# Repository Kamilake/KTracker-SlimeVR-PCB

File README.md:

# Move to the [FineMotion!](https://github.com/Kamilake/FineMotion-Tracker)
This repo is old and I created a new tracker. For non-maintenance purposes, go to:   
https://github.com/Kamilake/FineMotion-Tracker

# KTracker-SlimeVR-PCB
ESP8266 Attitude Tracker for SlimeVR

Full SMT PCB operating in MPU-6050 + QMC5883L 9DoF mode (or any breakout board compatible with GY-521)

Operate with all 5V chargers, including C to C PD chargers.

You can use it simply by ordering it from the fabricator

M.2 SSD size ultra-small form factor, Smallest size that can fit 18650!

## Available Battery

You can use any battery if you don't use the included modeling. or
1. 052050,052070,102050,102070 Size Li-Po (1000mAh) with JST PH 2.0mm Connector
2. 18650 battery (up to 4200mAh) with THT PIN 18650 Battery holder
3. 3x 1.5v battery (cannot be charged)

## Available Equipment 

## License
**This hardware is licensed under the CERN-OHL-P v2 license**, which is a permissive,
non-viral and non-reciprocal open hardware license. Unlike software licenses like
MIT and Apache 2.0, it better handles the nuances of hardware and protects both
the licensor and licensee from patent lawsuits.

**Unless you explicitly state otherwise, any contribution intentionally submitted
for inclusion in this work by you, shall be licensed as above, without any
additional terms or conditions.**

### Conveying notice of License
Note that as part of the CERN-OHL-P v2 license, recipients of manufactured
hardware must also receive notice of the above license. One such
method of conveying the notice is to include a link to the original source repo,
or printing "Licensed under CERN-OHL-P v2" on the PCB silkscreen. For more info,
see [here](https://ohwr.org/project/cernohl/wikis/Documents/CERN-OHL-version-2).

This is conceptually similar to the MIT/Apache 2.0 Licenses, where the original
license must still be included as a notice even when the source is modified and
subsequently relicensed under different terms.

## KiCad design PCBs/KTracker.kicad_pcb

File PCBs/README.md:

# Custom assembly using Kikit JLC

Due to JLCPCB's new assembly policy, soldering on the bottom side or using a non-black PCB will incur additional charges.   
Bottom side soldering is not possible if the "Economic" assembly option is selected.   

As the bottom side soldering is only for the connector, manual assembly is recommended.   

## Panalize and Fab
```batch
kikit panelize ^
    -p :jlcTooling ^
    --layout "grid; rows: 5; cols: 10;" ^
    --source "tolerance: 1000mm" ^
    --tabs full ^
    --cuts vcuts ./KamiTrack.kicad_pcb ^
    KamiTrack_panel.kicad_pcb

kikit fab jlcpcb ^
    --assembly ^
    --schematic ./KamiTrack.kicad_sch ^
    --ignore J1 ^
    --no-drc ./KamiTrack_panel.kicad_pcb ^
    ./fab
```

## Only Fab

### Using internal MPU-6050+QMC5883L and bottom Lipo
```batch
kikit fab jlcpcb ^
    --assembly ^
    --schematic ./KamiTrack.kicad_sch ^
    --ignore BT1,J3,J4,J5 ^
    --no-drc ./KamiTrack.kicad_pcb ^
    "./Gerber/Using internal MPU-6050+QMC5883L and bottom Lipo"
```
### Using internal MPU-6050+QMC5883L and Left side Lipo
```batch
kikit fab jlcpcb ^
    --assembly ^
    --schematic ./KamiTrack.kicad_sch ^
    --ignore BT1,J1,J4,J5 ^
    --no-drc ./KamiTrack.kicad_pcb ^
    "./Gerber/Using internal MPU-6050+QMC5883L and Left side Lipo"
```

### Using GY-521 and bottom Lipo
```batch
kikit fab jlcpcb ^
    --assembly ^
    --schematic ./KamiTrack.kicad_sch ^
    --ignore U8,U3,R20,R21,C16,C12,C11,R12,R11,BT1,J3,J4,J5 ^
    --no-drc ./KamiTrack.kicad_pcb ^
    "./Gerber/Using GY-521 and bottom Lipo"

```

### Using GY-521 and 18650
```batch
kikit fab jlcpcb ^
    --assembly ^
    --schematic ./KamiTrack.kicad_sch ^
    --ignore U8,U3,R20,R21,C16,C12,C11,R12,R11,J1,J3,J4,J5 ^
    --no-drc ./KamiTrack.kicad_pcb ^
    "./Gerber/Using GY-521 and 18650"

```

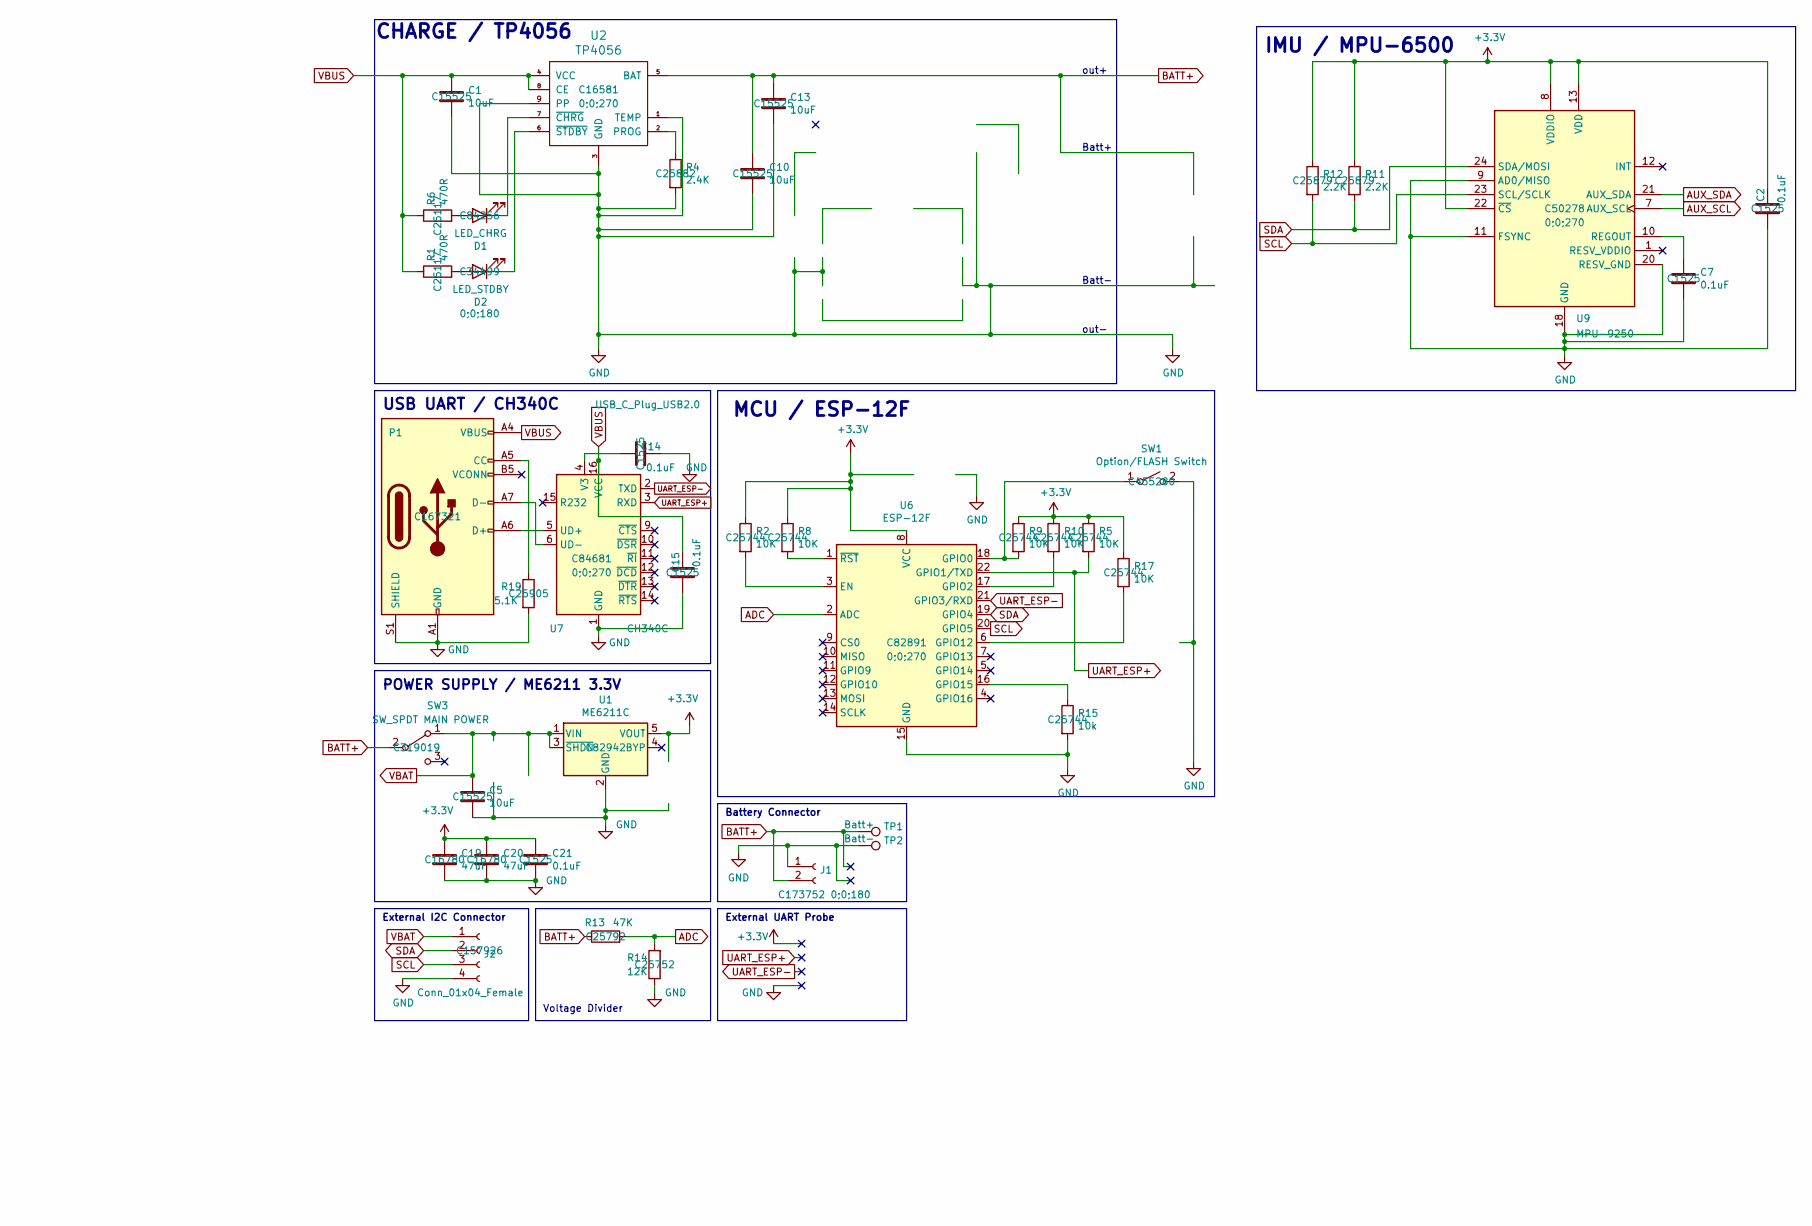
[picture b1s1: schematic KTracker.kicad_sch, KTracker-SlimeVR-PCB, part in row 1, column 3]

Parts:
C1, C5, C10, C13: 10uF; C_0402_1005Metric; LCSC C15525
C2, C7, C14, C15, C21: 0.1uF; C_0402_1005Metric; LCSC C1525
C19, C20: 47uF; C_0805_2012Metric; LCSC C16780
D1: LED_CHRG; LED_0805_2012Metric; LCSC C84256
D2: LED_STDBY; LED_0805_2012Metric; LCSC C34499
J1: Conn_01x02_Female; JST_PH_S2B-PH-K_1x02_P2.00mm_Horizontal; LCSC C173752
J2: Conn_01x04_Female; JST_PH_S4B-PH-K_1x04_P2.00mm_Horizontal; LCSC C157926
P1: USB_C_Plug_USB2.0; USB_C_Receptacle_HRO_TYPE-C-31-M-12; LCSC C167321
R1, R6: 470R; R_0402_1005Metric; LCSC C25117
R2, R5, R8, R9, R10, R17: 10K; R_0402_1005Metric; LCSC C25744
R4: 2.4K; R_0402_1005Metric; LCSC C25882
R11, R12: 2.2K; R_0402_1005Metric; LCSC C25879
R13: 47K; R_0402_1005Metric; LCSC C25792
R14: 12K; R_0402_1005Metric; LCSC C25752
R15: 10k; R_0402_1005Metric; LCSC C25744
R19: 5.1K; R_0402_1005Metric; LCSC C25905
SW1: Option/FLASH Switch; TS-1088R; LCSC C455280
SW3: SW_SPDT MAIN POWER; SW_SPDT_PCM12; LCSC C319019
TP1: Batt+; Pin_D0.9mm_L10.0mm_W2.4mm_FlatFork
TP2: Batt-; Pin_D0.9mm_L10.0mm_W2.4mm_FlatFork
U1: ME6211C; SOT-23-5; LCSC C82942
U2: TP4056; HSOP-8-1EP_3.9x4.9mm_P1.27mm_EP2.41x3.1mm_ThermalVias; LCSC C16581
U6: ESP-12F; ESP-12E; LCSC C82891
U7: CH340C; SOIC-16_3.9x9.9mm_P1.27mm; LCSC C84681
U9: MPU-9250; InvenSense_QFN-24_3x3mm_P0.4mm; LCSC C50278

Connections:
+3V3: C2.2, C19.1, C20.1, C21.1, R2.1, R5.1, R8.1, R9.1, R10.1, R11.1, R12.1, R17.1, U1.5 (VOUT), U6.8 (VCC), U9.8 (VDDIO), U9.13 (VDD), U9.22 (~CS)
ADC: R13.2, R14.2, U6.2 (ADC)
AUX_SCL: U9.7 (AUX_SCL)
AUX_SDA: U9.21 (AUX_SDA)
BATT+: C10.1, C13.1, J1.2, R13.1, SW3.2 (B), TP1.1, U2.5 (BAT)
GND: C1.2, C2.1, C5.2, C7.2, C10.2, C13.2, C14.2, C15.1, C19.2, C20.2, C21.2, J1.1, J2.4, P1.A1 (GND), P1.A12 (GND), P1.B1 (GND), P1.B12 (GND), P1.S1 (SHIELD), R4.2, R14.1, R15.2, R19.2, SW1.2 (B), TP2.1, U1.2 (GND), U2.1 (TEMP), U2.3 (GND), U2.9 (PP), U6.15 (GND), U7.1 (GND), U9.9 (AD0/MISO), U9.11 (FSYNC), U9.18 (GND), U9.20 (RESV_GND)
unnamed: C7.1, U9.10 (REGOUT)
unnamed: C14.1, U7.4 (V3)
unnamed: D1.1 (K), U2.7 (~CHRG)
unnamed: D1.2 (A), R6.2
unnamed: D2.1 (K), U2.6 (~STDBY)
unnamed: D2.2 (A), R1.2
unnamed: P1.A5 (CC), R19.1
unnamed: P1.A6 (D+), U7.5 (UD+)
unnamed: P1.A7 (D-), U7.6 (UD-)
unnamed: R2.2, U6.3 (EN)
unnamed: R4.1, U2.2 (PROG)
unnamed: R8.2, U6.1 (~RST)
unnamed: R9.2, SW1.1 (A), U6.18 (GPIO0)
unnamed: R10.2, U6.17 (GPIO2)
unnamed: R15.1, U6.16 (GPIO15)
unnamed: R17.2, U6.6 (GPIO12)
SCL: J2.3, R12.2, U6.20 (GPIO5), U9.23 (SCL/SCLK)
SDA: J2.2, R11.2, U6.19 (GPIO4), U9.24 (SDA/MOSI)
UART_ESP+: R5.2, U6.22 (GPIO1/TXD), U7.3 (RXD)
UART_ESP-: U6.21 (GPIO3/RXD), U7.2 (TXD)
VBAT: C5.1, J2.1, SW3.1 (A), U1.1 (VIN), U1.3 (~SHDN)
VBUS: C1.1, C15.2, P1.A4 (VBUS), P1.A9 (VBUS), P1.B4 (VBUS), P1.B9 (VBUS), R1.1, R6.1, U2.4 (VCC), U2.8 (CE), U7.16 (VCC)

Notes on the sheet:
Voltage Divider
Batt-
External UART Probe
MCU / ESP-12F
External I2C Connector
IMU / MPU-6500
POWER SUPPLY / ME6211 3.3V
out+
Batt+
CHARGE / TP4056
USB UART / CH340C
Battery Connector
out-

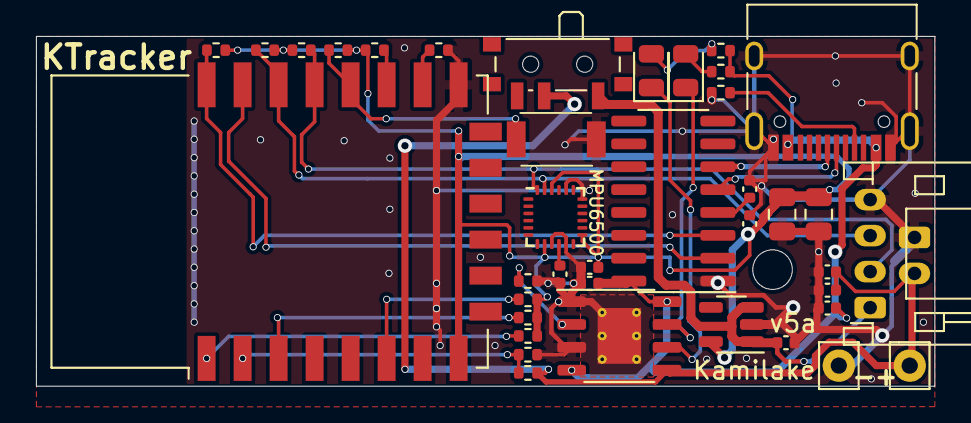
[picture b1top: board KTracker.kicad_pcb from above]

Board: 2 copper layers, 49.9 x 19.4 mm, 40 parts (1 on the bottom side), 26 nets.

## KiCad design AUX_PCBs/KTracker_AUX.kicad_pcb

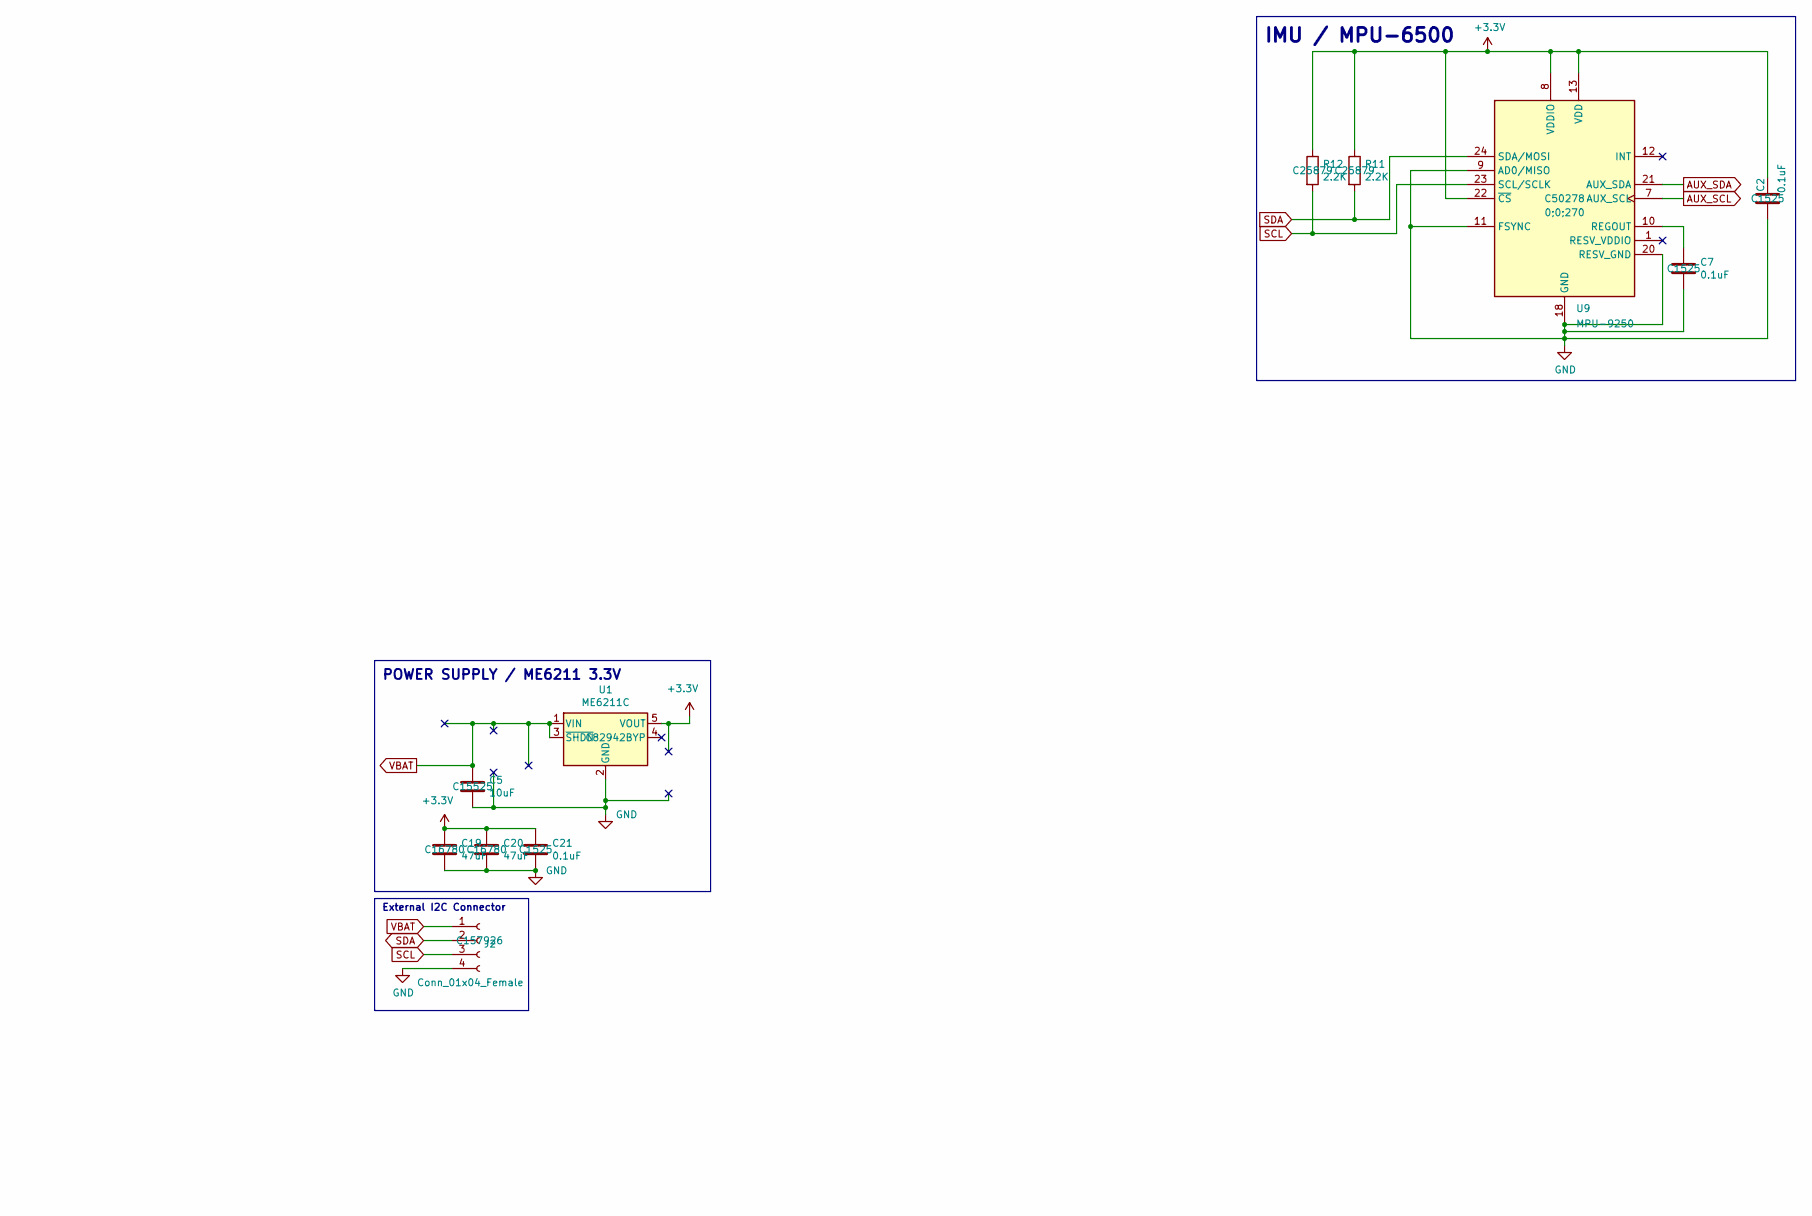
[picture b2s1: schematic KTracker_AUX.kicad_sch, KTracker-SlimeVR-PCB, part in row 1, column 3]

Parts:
C2, C7, C21: 0.1uF; C_0402_1005Metric; LCSC C1525
C5: 10uF; C_0402_1005Metric; LCSC C15525
C19, C20: 47uF; C_0805_2012Metric; LCSC C16780
J2: Conn_01x04_Female; JST_PH_S4B-PH-K_1x04_P2.00mm_Horizontal; LCSC C157926
R11, R12: 2.2K; R_0402_1005Metric; LCSC C25879
U1: ME6211C; SOT-23-5; LCSC C82942
U9: MPU-9250; InvenSense_QFN-24_3x3mm_P0.4mm; LCSC C50278

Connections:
+3V3: C2.2, C19.1, C20.1, C21.1, R11.1, R12.1, U1.5 (VOUT), U9.8 (VDDIO), U9.13 (VDD), U9.22 (~CS)
AUX_SCL: U9.7 (AUX_SCL)
AUX_SDA: U9.21 (AUX_SDA)
GND: C2.1, C5.2, C7.2, C19.2, C20.2, C21.2, J2.4, U1.2 (GND), U9.9 (AD0/MISO), U9.11 (FSYNC), U9.18 (GND), U9.20 (RESV_GND)
unnamed: C7.1, U9.10 (REGOUT)
SCL: J2.3, R12.2, U9.23 (SCL/SCLK)
SDA: J2.2, R11.2, U9.24 (SDA/MOSI)
VBAT: C5.1, J2.1, U1.1 (VIN), U1.3 (~SHDN)

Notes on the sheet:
External I2C Connector
IMU / MPU-6500
POWER SUPPLY / ME6211 3.3V

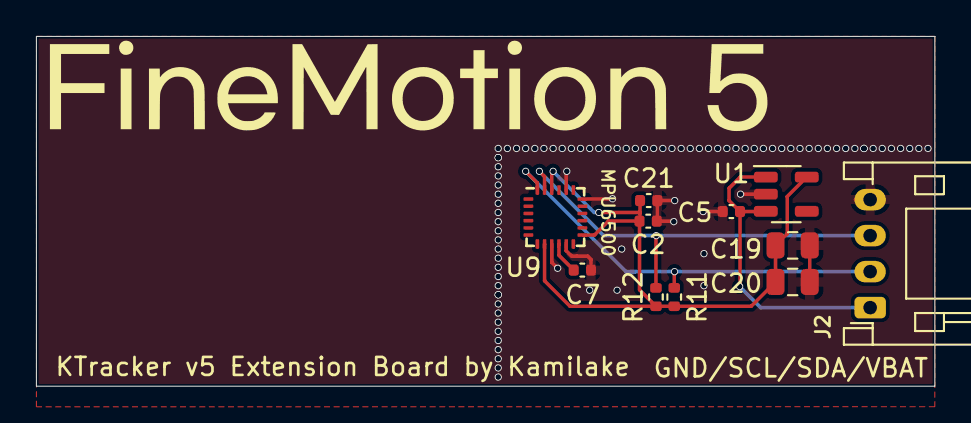
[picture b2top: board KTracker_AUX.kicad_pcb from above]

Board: 2 copper layers, 49.9 x 19.4 mm, 11 parts (0 on the bottom side), 6 nets.

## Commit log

2022-04-01 Add 3D Models
2022-04-06 ignore caches
2022-04-06 pcb thickness 1.6->1.2
2022-04-06 update licence
2022-04-06 Update License
2022-04-07 Added sheet description
2022-06-29 custom assembly guide
2022-06-29 Rename Kikit build.md to README.md
2022-06-29 QMC5883L
2022-06-29 Left side Lipo
2022-06-29 Standby LED Change to C34499
2022-06-29 Rename to kamitrack
2022-06-30 JLCPCB_CORRECTION
2022-06-30 PCBs/Gerber/
2022-07-28 add JLCPCB_CORRECTION
2022-07-28 add more JLCPCB_CORRECTION
2022-07-28 JLCPCB_CORRECTION;;;;;;;;;;;
2022-07-28 THIS IS VERY CURRECT JLCPCB_CORRECTION I SWEAR
2022-08-12 Rename KamiTrack-cache.lib to KTracker-cache.lib
2022-08-12 Rename KamiTrack.kicad_pcb to KTracker.kicad_pcb
2022-08-12 Rename KamiTrack.kicad_pro to KTracker.kicad_pro
2022-08-12 Rename KamiTrack.kicad_sch to KTracker.kicad_sch
2022-08-12 Replace KamiTrack to KTracker
2022-08-18 #auto_saved_files#
2022-08-18 MPU 6500!!
2022-08-24 clear silk
2022-08-26 add TS-1088R STEP
2022-09-21 6050->6500
2022-09-24 Finemotion_aux

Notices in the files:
AUX_PCBs/KTracker_AUX.kicad_sch:
Licensed under CERN-OHL-P v2 or later
